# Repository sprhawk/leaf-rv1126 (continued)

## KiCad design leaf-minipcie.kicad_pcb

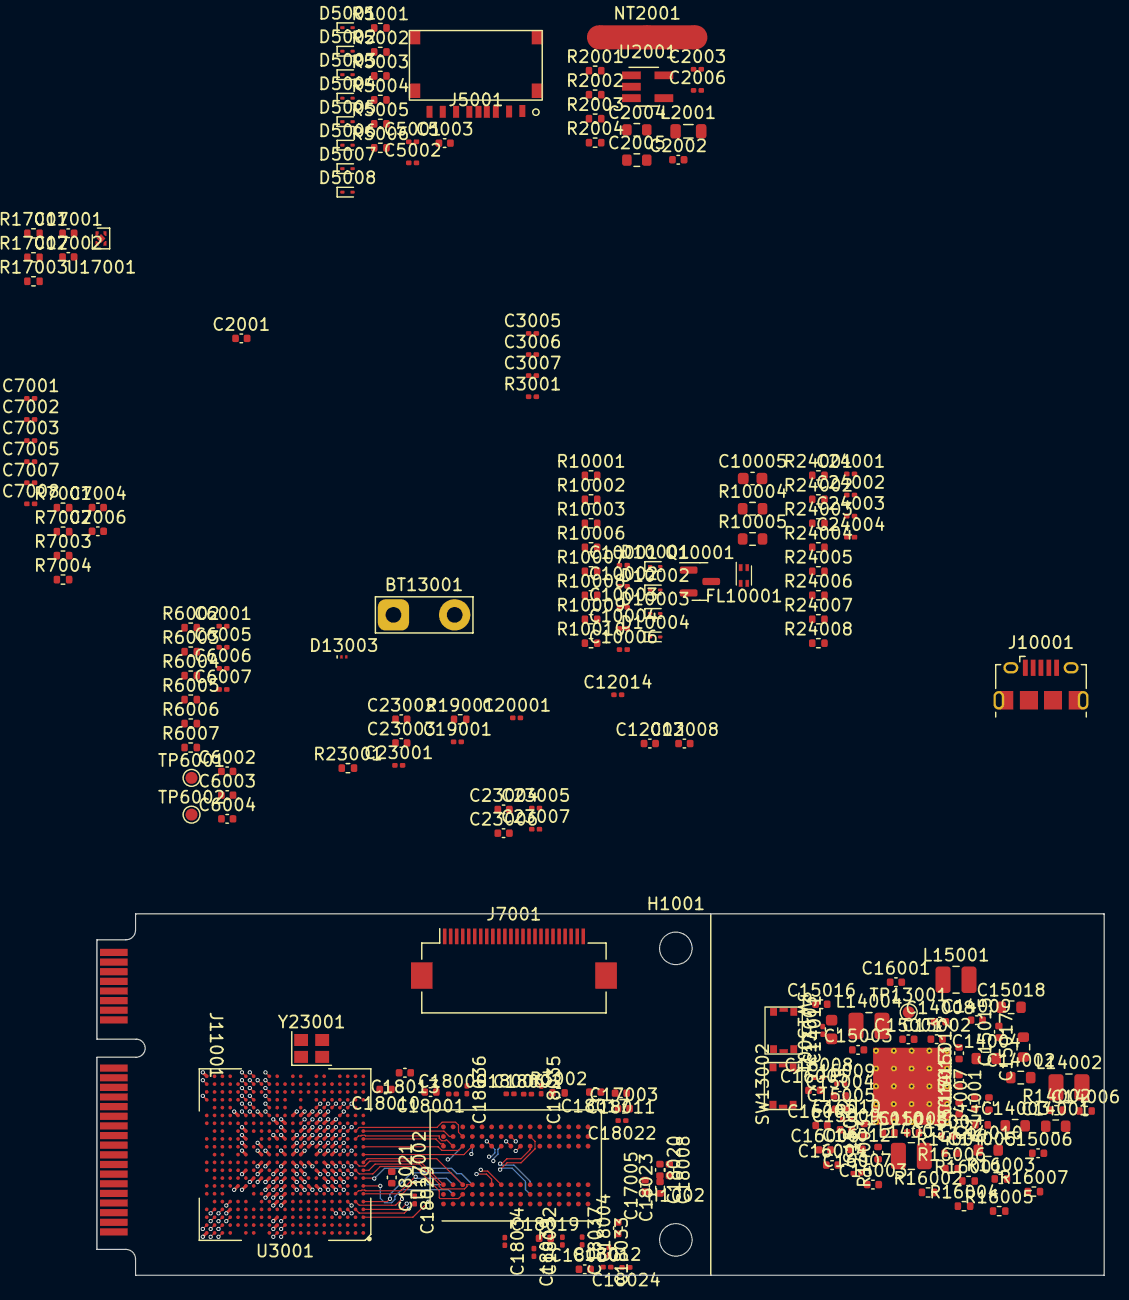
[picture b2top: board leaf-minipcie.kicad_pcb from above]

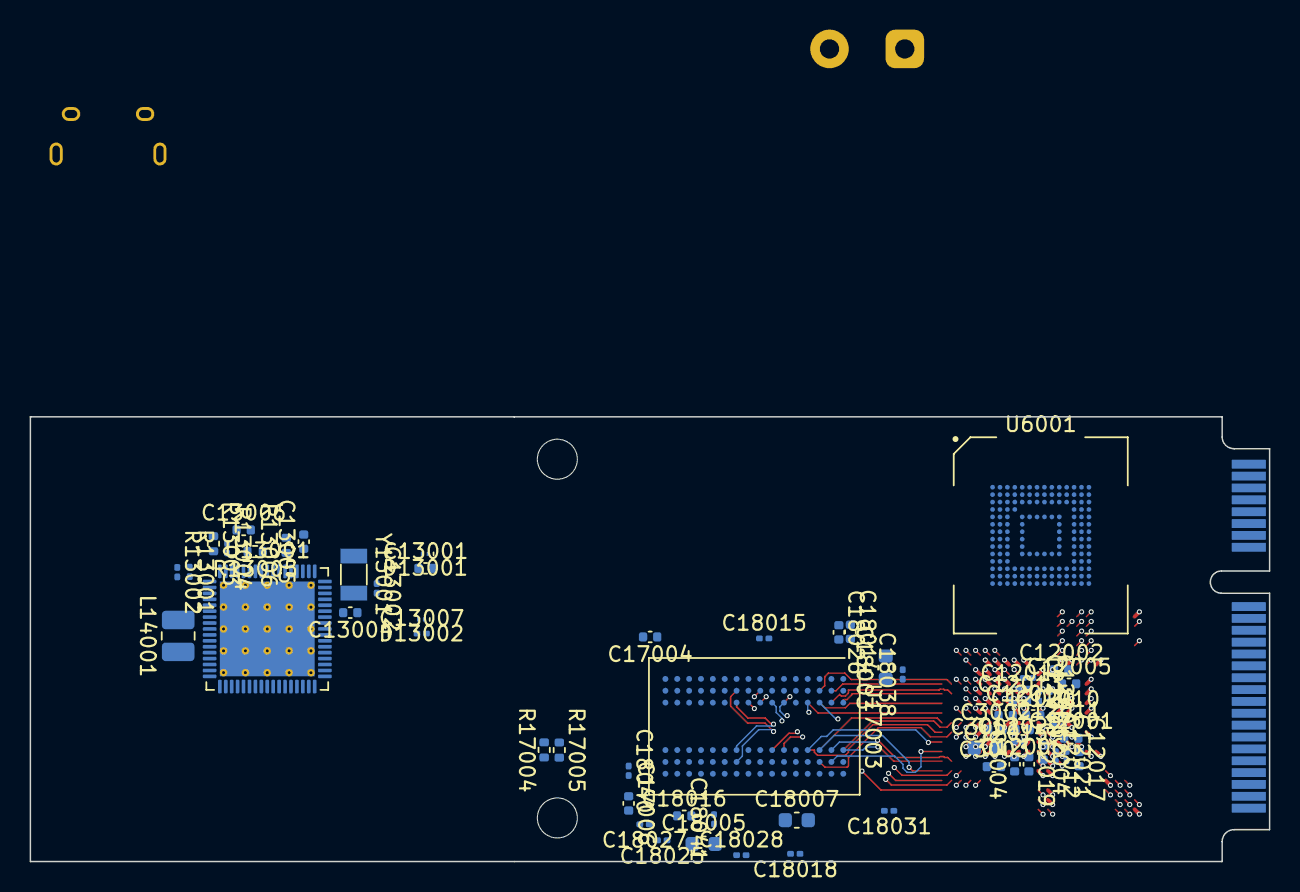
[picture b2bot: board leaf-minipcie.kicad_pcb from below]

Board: 6 copper layers, 83.6 x 30.0 mm, 275 parts (61 on the bottom side), 212 nets.

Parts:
BT13001: Battery_Cell; TestPoint_2Pads_Pitch5.08mm_Drill1.3mm
C2001, C5003, C12001, C12002, C12003, C12008, C12013, C12017, C14007, C14008, C14009, C15005, C16001: 10uF X5R 10V; C_0402_1005Metric
C2002, C18004, C18008, C18010, C18011, C18013, C18014, C18016, C18019, C18020, C18023, C18026: 100nF X5R 10V; C_0402_1005Metric
C2003, C13002, C13003: 22pF 50V C0G; C_0201_0603Metric
C2004, C2005, C14001, C14002, C14003, C14004, C14010, C15017, C15018: 22uF X5R 10V; R_0603_1608Metric
C2006, C3005, C3006, C3007, C5001, C5002, C6001, C6005, C6006, C6007, C7001, C7002, C7003, C7005, C7007, C7008, C10001, C10002, C10003, C10004, C10006, C12007, C12009, C12010, C12011, C12012, C12014, C12016, C12018, C12021, C12022, C13007, C16009, C16010, C18002, C18006, C18009, C18012, C18015, C18018, C18022, C18024, C18025, C18027, C18028, C18029, C18031, C18032, C18033, C18034, C18035, C18036, C18037, C18038, C18039, C18040, C18041, C19001, C20001, C23001, C23005, C23007: 100nF X5R 6.3V; C_0201_0603Metric
C3001: 10uF X5R 6.3V; C_0603_1608Metric
C3002, C3003, C3004, C12004, C12005, C12006, C12015, C12019, C12020, C13004, C13005, C15001, C15002, C15003, C15004, C16002, C16004, C16005, C23004, C23006: 1uF X5R 6.3V; C_0402_1005Metric
C6002, C6003, C6004, C15009, C18001, C18017: 4.7uF X5R 10V; C_0402_1005Metric
C7004, C7006: 10uF X5R 6.3V; C_0402_1005Metric
C10005, C14011: 22uF X5R 10V; C_0603_1608Metric
C13001: 100nF X5R 6.3V; C_0402_1005Metric
C13006: 10nF 25V X5R; C_0402_1005Metric
C14005, C14006, C14012: 10uF X5R 6.3V; R_0402_1005Metric
C15006, C15007, C15008, C15010, C15011, C15012, C15013, C15014, C15015, C15016: 1uF X5R 10V; C_0402_1005Metric
C16003, C16006: 2.2uF X5R 10V; C_0402_1005Metric
C16007, C16008: 27pF C0G 50V; C_0201_0603Metric
C17001, C17002: 1uF ±10% 6.3V; C_0402_1005Metric
C17003, C17005: 10nF X5R 50V; C_0402_1005Metric
C17004, C17006, C18021, C18030: 1nF X5R 50V; C_0402_1005Metric
C18003, C18005, C18007: 22uF X5R 6.3V; C_0603_1608Metric
C23002, C23003: 10pF 50V C0G +-1%; C_0402_1005Metric
C24001, C24003: 1nF X5R 25V; C_0201_0603Metric
C24002, C24004: 100pF C0G 50V; C_0201_0603Metric
D5001, D5002, D5003, D5004, D5005, D5006, D5007, D5008, D10001, D10002, D10003, D10004: ESD9B5.0ST5G; D_SOD-923
D13001: ESD 3.3V; Nexperia_DSN0603-2_0.6x0.3mm_P0.4mm
D13002, D13003: ESD 5.0V; Nexperia_DSN0603-2_0.6x0.3mm_P0.4mm
FL10001: Filter_EMI_CommonMode; L_CommonModeChoke_Coilcraft_0603USB
H1001, H1002: MountingHole; MountingHole_2.7mm_M2.5
J5001: Micro_SD_Card_Det1; microSD
J7001: MIPI-CSI; Hirose_FH12-24S-0.5SH_1x24-1MP_P0.50mm_Horizontal
J10001: USB_OTG; USB_Micro-B_Amphenol_10118194_Horizontal
J11001: mini PCIe Card edge; PCIe_MiniCard
L2001: 2.2uH 0.102 ohm 2.30A; L_0805_2012Metric
L14001, L14002, L14003, L14004, L15001: 470nH 4.53A 0.035ohm; L_1008_2520Metric
NT2001: NetTie_3_Tee; NetTie-3_SMD_Pad2.0mm
Q10001: Q_PNP_BEC; SOT-23
R2001: 56K 1%; R_0402_1005Metric
R2002, R10008, R14001, R14002: 100R 5%; R_0402_1005Metric
R2003: 43.2K 1%; R_0402_1005Metric
R2004: 115K 1%; R_0402_1005Metric
R3001: 240R 1%; R_0201_0603Metric
R3002, R6004, R6005, R7003, R7004, R16007, R19001: 0R 5%; R_0402_1005Metric
R5001, R5002, R5003, R5004, R5005, R5006, R13003, R16001, R16002, R16003, R16004, R16005, R16006, R23001: 22R 5%; R_0402_1005Metric
R6002, R6003, R6006, R6007: 4.7K 5%; R_0402_1005Metric
R7001, R7002, R10001: 2.2K 5%; R_0402_1005Metric
R10002: 1K 5%; R_0402_1005Metric
R10003: 220R 5%; R_0402_1005Metric
R10004, R10005: 2.2R 5%; R_0603_1608Metric
R10006, R10007: 200R 1%; R_0402_1005Metric
R10009: 18K 1%; R_0402_1005Metric
R10010, R17004, R17005: 10K 1%; R_0402_1005Metric
R13001, R13002: 2.2kΩ ±5%; R_0201_0603Metric
R13004: 4.7K 5%; R_0201_0603Metric
R13005: 450K 1%; R_0402_1005Metric
R13006: 47K 1%; R_0402_1005Metric
R14003: 120K 1%; R_0402_1005Metric
R14004: 110K 1%; R_0402_1005Metric
R17001, R17002, R17003: 240R 1%; R_0402_1005Metric
R24001, R24002, R24005, R24006: 1K 1%; R_0402_1005Metric
R24003, R24004, R24007, R24008: 49.9R 1%; R_0402_1005Metric
SW13001, SW13002: SKSGPAE010; SW_SPST_ALPS_SKSG_3.9x2.7mm
TP6001, TP6002, TP13001: TestPoint; TestPoint_Pad_D1.0mm
U2001: BL8039; SOT-23-5_HandSoldering
U3001: rv1126/rv1109; Rockchip_RV1126_FCCSP409LD_14.0x14.0mm
U6001: MTFC4GACAJCN; Micron_eMMC_FBGA-153_11.5x13.0mm
U13001: RK809-2; QFN-68-1EP_8x8mm_P0.4mm_EP6.4x6.4mm_ThermalVias
U17001: NCP114AMX250TCG; OnSemi_XDFN4-1EP_1.0x1.0mm_EP0.52x0.52mm
U17002, U17003: Samsung K4A4G165WE-BCRC; Micron_FBGA-96_9x14mm_Layout9x16_P0.8mm
Y13001: 32.768kHz ±20ppm 12.5pF; Crystal_SMD_3215-2Pin_3.2x1.5mm
Y23001: 24MHz ±10ppm 10pF; Crystal_SMD_2520-4Pin_2.5x2.0mm

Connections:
/DDR/DDR4_A0: U3001.C9 (LPDDR4_CKE1_A/DDR4_A0/LPDDR3_A3/DDR3_A3), U17002.P3 (A0), U17003.P3 (A0)
/DDR/DDR4_A1: U3001.B7 (LPDDR4_CKE0_B/DDR4_A1/DDR3_BA1), U17002.P7 (A1), U17003.P7 (A1)
/DDR/DDR4_A2: U3001.B11 (LPDDR4_A4_A/DDR4_A2/LPDDR3_A9/DDR3_A9), U17002.R3 (A2), U17003.R3 (A2)
/DDR/DDR4_A3: U3001.B6 (LPDDR4_A5_B/DDR4_A3/DDR3_A15), U17002.N7 (A3), U17003.N7 (A3)
/DDR/DDR4_A4: U3001.A9 (LPDDR4_CLKP_A/DDR4_A4/LPDDR3_A6/DDR3_A6), U17002.N3 (A4), U17003.N3 (A4)
/DDR/DDR4_A5: U3001.A7 (LPDDR4_ODT0_B/DDR4_A5/DDR3_A12), U17002.P8 (A5), U17003.P8 (A5)
/DDR/DDR4_A6: U3001.C8 (LPDDR4_A0_A/DDR4_A6/DDR3_BA2), U17002.P2 (A6), U17003.P2 (A6)
/DDR/DDR4_A7: U3001.B8 (LPDDR4_ODT0_A/DDR4_A7/LPDDR3_A4/DDR3_A4), U17002.R8 (A7), U17003.R8 (A7)
/DDR/DDR4_A8: U3001.A8 (LPDDR4_CKE0_A/DDR4_A8/LPDDR3_A1/DDR3_A1), U17002.R2 (A8), U17003.R2 (A8)
/DDR/DDR4_A9: U3001.B9 (LPDDR4_A5_A/DDR4_A9/LPDDR3_A5/DDR3_A5), U17002.R7 (A9), U17003.R7 (A9)
/DDR/DDR4_A10: U3001.A10 (LPDDR4_CLKN_A/DDR4_A10/LPDDR3_A8/DDR3_A8), U17002.M3 (A10/AP), U17003.M3 (A10/AP)
/DDR/DDR4_A11: U3001.C11 (LPDDR4_A2_A/DDR4_A11/LPDDR3_A7/DDR3_A7), U17002.T2 (A11), U17003.T2 (A11)
/DDR/DDR4_A12: U3001.D7 (LPDDR4_A1_A/DDR4_A12/DDR3_RASn), U17002.M7 (A12/~BC), U17003.M7 (A12/~BC)
/DDR/DDR4_A13: U3001.A12 (LPDDR4_A3_A/DDR4_A13/DDR3_A13), U17002.T8 (A13), U17003.T8 (A13)
/DDR/DDR4_A14_~WE: U3001.A11 (LPDDR4_CS1n_B/DDR4_A14_Wen/DDR3_A14), U17002.L2 (A14/~WE), U17003.L2 (A14/~WE)
/DDR/DDR4_A15_~CAS: U3001.B5 (LPDDR4_A0_B/DDR4_A15_CASn/DDR3_A10), U17002.M8 (A15/~CAS), U17003.M8 (A15/~CAS)
/DDR/DDR4_A16_~RAS: U3001.B10 (LPDDR4_CS0n_B/DDR4_A16_RASn/DDR3_A11), U17002.L8 (A16/~RAS), U17003.L8 (A16/~RAS)
/DDR/DDR4_BA0: U3001.E7 (LPDDR4_CS0n_A/DDR4_BA0/LPDDR3_CS1n/DDR3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), U17002.N2 (BA0), U17003.N2 (BA0)
/DDR/DDR4_BA1: U3001.A6 (LPDDR4_CKE1_B/DDR4_BA1/DDR3_WEn), U17002.N8 (BA1), U17003.N8 (BA1)
/DDR/DDR4_BG0: U3001.D6 (LPDDR4_CS1n_A/DDR4_BG0/LPDDR3_ODT1/DDR3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), U17002.M2 (BG0), U17003.M2 (BG0)
/DDR/DDR4_CKE: U3001.C6 (LPDDR4_A1_B/DDR4_CKE/DDR3_CASn), U17002.K2 (CKE), U17003.K2 (CKE)
/DDR/DDR4_CLKN: R24004.1, R24008.1, U3001.D5 (LPDDR4_CLKN_B/DDR4_CLKN/LPDDR3_CLKN/DDR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), U17002.K8 (CK#), U17003.K8 (CK#)
/DDR/DDR4_CLKP: R24003.1, R24007.1, U3001.D4 (LPDDR4_CLKP_B/DDR4_CLKP/LPDDR3_CLKP/DDR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), U17002.K7 (CK), U17003.K7 (CK)
/DDR/DDR4_D0: U3001.K4 (DDR_DQ0/LPDDR4_D8_A/LPDDR3_D2), U17002.J3 (DQ6)
/DDR/DDR4_D1: U3001.J4 (DDR_DQ1/LPDDR4_D9_A/LPDDR3_D6), U17002.G2 (DQ0)
/DDR/DDR4_D2: U3001.P4 (DDR_DQ2/LPDDR4_D10_A/LPDDR3_D4), U17002.H7 (DQ3)
/DDR/DDR4_D3: U3001.N4 (DDR_DQ3/LPDDR4_D11_A/LPDDR3_D0), U17002.H8 (DQ5)
/DDR/DDR4_D4: U3001.J3 (DDR_DQ4/LPDDR4_D12_A/LPDDR3_D3), U17002.H2 (DQ4)
/DDR/DDR4_D5: U3001.K3 (DDR_DQ5/LPDDR4_D13_A/LPDDR3_D7), U17002.H3 (DQ2)
/DDR/DDR4_D6: U3001.M4 (DDR_DQ6/LPDDR4_D14_A/LPDDR3_D5), U17002.J7 (DQ7)
/DDR/DDR4_D7: U3001.P3 (DDR_DQ7/LPDDR4_D15_A/LPDDR3_D1), U17002.F7 (DQ1)
/DDR/DDR4_D8: U3001.D2 (DDR_DQ8/LPDDR4_D10_B/LPDDR3_D0), U17003.C3 (DQ10)
/DDR/DDR4_D9: U3001.D1 (DDR_DQ9/LPDDR4_D1_B/LPDDR3_D11), U17003.D3 (DQ14)
/DDR/DDR4_D10: U3001.H2 (DDR_DQ10/LPDDR4_D2_B/LPDDR3_D8), U17003.C8 (DQ13)
/DDR/DDR4_D11: U3001.H1 (DDR_DQ11/LPDDR4_D3_B/LPDDR3_D9), U17003.D7 (DQ15)
/DDR/DDR4_D12: U3001.G1 (DDR_DQ12/LPDDR4_D4_B/LPDDR3_D12), U17003.B8 (DQ9)
/DDR/DDR4_D13: U3001.E1 (DDR_DQ13/LPDDR4_D5_B/LPDDR3_D13), U17003.C7 (DQ11)
/DDR/DDR4_D14: U3001.C1 (DDR_DQ14/LPDDR4_D6_B/LPDDR3_D14), U17003.C2 (DQ12)
/DDR/DDR4_D15: U3001.C2 (DDR_DQ15/LPDDR4_D7_B/LPDDR3_D15), U17003.A3 (DQ8)
/DDR/DDR4_D16: U3001.K1 (DDR_DQ16/LPDDR4_D0_A/LPDDR3_D19), U17002.C3 (DQ10)
/DDR/DDR4_D17: U3001.K2 (DDR_DQ17/LPDDR4_D1_A/LPDDR3_D18), U17002.A3 (DQ8)
/DDR/DDR4_D18: U3001.J1 (DDR_DQ18/LPDDR4_D2_A/LPDDR3_D23), U17002.D3 (DQ14)
/DDR/DDR4_D19: U3001.J2 (DDR_DQ19/LPDDR4_D3_A/LPDDR3_D22), U17002.C2 (DQ12)
/DDR/DDR4_D20: U3001.P2 (DDR_DQ20/LPDDR4_D4_A/LPDDR3_D21), U17002.C8 (DQ13)
/DDR/DDR4_D21: U3001.L1 (DDR_DQ21/LPDDR4_D5_A/LPDDR3_D16), U17002.D7 (DQ15)
/DDR/DDR4_D22: U3001.M1 (DDR_DQ22/LPDDR4_D6_A/LPDDR3_D17), U17002.C7 (DQ11)
/DDR/DDR4_D23: U3001.P1 (DDR_DQ23/LPDDR4_D7_A/LPDDR3_D20), U17002.B8 (DQ9)
/DDR/DDR4_D24: U3001.A2 (DDR_DQ24/LPDDR4_D8_B/LPDDR3_D30), U17003.H2 (DQ4)
/DDR/DDR4_D25: U3001.A3 (DDR_DQ25/LPDDR4_D9_B/LPDDR3_D31), U17003.G2 (DQ0)
/DDR/DDR4_D26: U3001.G4 (DDR_DQ26/LPDDR4_D10_B/LPDDR3_D28), U17003.F7 (DQ1)
/DDR/DDR4_D27: U3001.F4 (DDR_DQ27/LPDDR4_D11_B/LPDDR3_D29), U17003.J7 (DQ7)
/DDR/DDR4_D28: U3001.H3 (DDR_DQ28/LPDDR4_D12_B/LPDDR3_D24), U17003.H8 (DQ5)
/DDR/DDR4_D29: U3001.G3 (DDR_DQ29/LPDDR4_D13_B/LPDDR3_D25), U17003.H7 (DQ3)
/DDR/DDR4_D30: U3001.B1 (DDR_DQ30/LPDDR4_D14_B/LPDDR3_D26), U17003.H3 (DQ2)
/DDR/DDR4_D31: U3001.B2 (DDR_DQ31/LPDDR4_D15_B/LPDDR3_D27), U17003.J3 (DQ6)
/DDR/DDR4_DM0: U3001.N3 (DDR_DM0/LPDDR4_DM1_A/LPDDR3_DM0), U17002.E7 (NF/~LDM/~LDBI)
/DDR/DDR4_DM1: U3001.E2 (DDR_DM1/LPDDR4_DM0_B/LPDDR3_DM1), U17003.E7 (NF/~LDM/~LDBI)
/DDR/DDR4_DM2: U3001.M2 (DDR_DM2/LPDDR4_DM0_A/LPDDR3_DM2), U17002.E2 (NF/~UDM/~UDBI)
/DDR/DDR4_DM3: U3001.B3 (DDR_DM3/LPDDR4_DM1_B/LPDDR3_DM3), U17003.E2 (NF/~UDM/~UDBI)
/DDR/DDR4_DQS0N: U3001.L3 (DDR_DQS0N/LPDDR4_DQS1N_A/LPDDR3_DQS0N), U17002.F3 (LDQS#)
/DDR/DDR4_DQS0P: U3001.L4 (DDR_DQS0P/LPDDR4_DQS1P_A/LPDDR3_DQS0P), U17002.G3 (LDQS)
/DDR/DDR4_DQS1N: U3001.F1 (DDR_DQS1N/LPDDR4_DQS0N_B/LPDDR3_DQS1N), U17003.A7 (UDQS#)
/DDR/DDR4_DQS1P: U3001.F2 (DDR_DQS1P/LPDDR4_DQS0P_B/LPDDR3_DQS01P), U17003.B7 (UDQS)
/DDR/DDR4_DQS2N: U3001.N1 (DDR_DQS2N/LPDDR4_DQS0N_A/LPDDR3_DQS2N), U17002.A7 (UDQS#)
/DDR/DDR4_DQS2P: U3001.N2 (DDR_DQS2P/LPDDR4_DQS0P_A/LPDDR3_DQS2P), U17002.B7 (UDQS)
/DDR/DDR4_DQS3N: U3001.E3 (DDR_DQS3N/LPDDR4_DQS1N_B/LPDDR3_DQS3N), U17003.F3 (LDQS#)
/DDR/DDR4_DQS3P: U3001.D3 (DDR_DQS3P/LPDDR4_DQS1P_B/LPDDR3_DQS3P), U17003.G3 (LDQS)
/DDR/DDR4_ODT0: U3001.A5 (LPDDR4_A4_B/DDR4_ODT0/LPDDR3_CS0n/DDR3_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), U17002.K3 (ODT), U17003.K3 (ODT)
/DDR/DDR4_~ACT: U3001.A4 (LPDDR4_A3_B/DDR4_ACTn/LPDDR3_CKE/DDR3_C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), U17002.L3 (~ACT), U17003.L3 (~ACT)
/DDR/DDR4_~CS0: U3001.B4 (LPDDR4_A2_B/DDR4_CS0n/LPDDR3_ODT0/DDR3_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), U17002.L7 (~CS), U17003.L7 (~CS)
/DDR/DDR Power/VCC25_DDR: C17002.1, C18001.1, C18004.2, C18008.2, C18011.2, C18014.2, C18017.1, C18020.2, C18023.2, C18026.2, U17001.1 (OUT), U17002.B1 (V_{PP}), U17002.R9 (V_{PP}), U17003.B1 (V_{PP}), U17003.R9 (V_{PP})
/DDR/DDR_VREFCA: C17003.1, C17004.1, C17005.1, C17006.1, R3002.2, R17004.2, R17005.1, U17002.M1 (V_{REFCA}), U17003.M1 (V_{REFCA})
/DDR/DDR_~RESET: C24001.1, C24003.1, U3001.C4 (DDR_RESETn), U17002.P1 (~RESET), U17003.P1 (~RESET)
/DDR/VREF_DDR: R3002.1, U3001.M6 (DDR_VREF)
/PMIC_CLK32K: R13003.1, U3001.AA3 (CLKI_CLKO_32K/GPIO0_A2_z)
/PMIC_I2C_SCL: R13002.2, U3001.AA7 (I2C0_SCL/GPIO0_B4_u), U13001.2 (SDA)
/PMIC_I2C_SDA: R13001.2, U3001.Y7 (I2C0_SDA/GPIO0_B5_u), U13001.1 (SCL)
/PMIC_INT: U3001.W10 (PMIC_INT/PWM7_IR_M0/GPIO0_B1_d), U13001.7 (INT)
/PMIC_RESET: C13001.1, C23001.1, D13001.2 (A2), R13004.2, R19001.1, SW13001.1, U3001.W7 (nPOR_u), U13001.67 (RESETB)
/PMIC_SLEEP: U3001.Y10 (PMIC_SLEEP/TSADC_SHUT_M1/PWM6_M0/GPIO0_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), U13001.49 (SLEEP)
/PMUIO0/SD_DET: D5001.1 (A1), J5001.9 (DET), U3001.U7 (SDMMC0_DET/GPIO0_A3_u)
/PMUIO1/FLASH_VOL_SEL: R6002.1, R6003.2, U3001.Y8 (FLASH_VOL_SEL/GPIO0_B3_d)
/Power/PMIC/RK809 Codec/I2S_LRCLK_TX: R16003.2, U13001.14 (LRCLK)
/Power/PMIC/RK809 Codec/I2S_MCLK: R16001.2, U13001.16 (MCLK)
/Power/PMIC/RK809 Codec/I2S_SCLK_TX: R16002.2, U13001.15 (BCLK)
/Power/PMIC/RK809 Codec/I2S_SDI0: R16005.2, U13001.18 (SDO/PDMDATA)
/Power/PMIC/RK809 Codec/I2S_SDO0: R16004.2, U13001.17 (SDI)
/Power/PMIC/RK809 Management/PWR_ON: C13007.1, D13002.2 (A2), SW13002.1, U13001.52 (PWRON)
/SoC OSC PLL/XIN24M: C23003.2, U3001.AA9 (XIN24M), Y23001.1
/SoC OSC PLL/XOUT24M: R23001.1, U3001.Y9 (XOUT24M)
/USB/OTG_DET_1V8: C10006.1, R10009.1, R10010.2, U3001.V5 (OTG_VBUS_1V8)
/USB/OTG_DM: FL10001.3, R10003.2, R10005.1, U3001.W4 (OTG_DM)
/USB/OTG_DP: FL10001.1, R10004.1, U3001.W3 (OTG_DP)
/USB/OTG_ID: R10008.1, U3001.Y3 (OTG_ID)
/USB/OTG_PORT_DM: D10004.1 (A1), FL10001.4, J10001.2 (D-), R10005.2
/USB/OTG_PORT_DP: D10002.1 (A1), FL10001.2, J10001.3 (D+), R10004.2
/USB_CTRL: R10001.2, U3001.AA4 (USB_CTRL/PMU_DEBUG/UART1_CTSN_M0/PWM3_I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)
/VCCIO1/EMMC_CLK: R6004.1, U6001.M6 (CLK)
/VCCIO1/EMMC_CMD: R6006.1, U3001.T4 (FLASH_WRn/EMMC_CMD/GPIO0_D5_u), U6001.M5 (CMD)
/VCCIO1/EMMC_D0: R6007.1, TP6001.1, U3001.W2 (FLASH_D0/EMMC_D0/GPIO0_C4_u), U6001.A3 (DATA0)
/VCCIO1/EMMC_D1: U3001.W1 (FLASH_D1/EMMC_D1/GPIO0_C5_u), U6001.A4 (DATA1)
/VCCIO1/EMMC_D2: U3001.V4 (FLASH_D2/EMMC_D2/GPIO0_C6_u), U6001.A5 (DATA2)
/VCCIO1/EMMC_D3: U3001.V3 (FLASH_D3/EMMC_D3/GPIO0_C7_u), U6001.B2 (DATA3)
/VCCIO1/EMMC_D4: U3001.V2 (FLASH_D4/EMMC_D4/GPIO0_D0_u), U6001.B3 (DATA4)
/VCCIO1/EMMC_D5: U3001.V1 (FLASH_D5/EMMC_D5/FSPI_CS1n/GPIO0_D1_u), U6001.B4 (DATA5)
/VCCIO1/EMMC_D6: U3001.U4 (FLASH_D6/EMMC_D6/GPIO0_D2_u), U6001.B5 (DATA6)
/VCCIO1/EMMC_D7: U3001.U3 (FLASH_D7/EMMC_D7/GPIO0_D3_u), U6001.B6 (DATA7)
/VCCIO1/EMMC_~RST: R6005.1, U6001.K5 (~RST)
/VCCIO2/A7_JTAG_TCK: R5005.1, U3001.V13 (SDMMC0_D2/UART3_RX_M1/A7_JTAG_TCK_M0/RI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)
/VCCIO2/A7_JTAG_TMS: R5006.1, U3001.U13 (SDMMC0_D3/UART3_TX_M1/A7_JTAG_TMS_M0/RI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)
/VCCIO2/RV_JTAG_TDI: R5002.1, U3001.Y13 (SDMMC0_CMD/UART3_CTSN_M1/RISC-V_JTAG_TD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)
/VCCIO2/RV_JTAG_TDO: R5001.1, U3001.AA13 (SDMMC0_CLK/UART3_RTSN_M1/RISC-V_JTAG_TD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)
/VCCIO2/RV_JTAG_TRSTn: R5004.1, U3001.W13 (SDMMC0_D1/TEST_CLK0_OUT/UART2_TX_M0/RIS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)
/VCCIO2/SD_CLK: D5004.1 (A1), J5001.5 (CLK), R5001.2
/VCCIO2/SD_CMD: D5006.1 (A1), J5001.3 (CMD), R5002.2
/VCCIO2/SD_D0: D5003.1 (A1), J5001.7 (DAT0), R5003.2
/VCCIO2/SD_D1: D5002.1 (A1), J5001.8 (DAT1), R5004.2
/VCCIO2/SD_D2: D5008.1 (A1), J5001.1 (DAT2), R5005.2
/VCCIO2/SD_D3: D5007.1 (A1), J5001.2 (DAT3/CD), R5006.2
/VCCIO4/MIPI_CSI_AVDD_0V8: C7003.1, R7004.2, U3001.T15 (MIPI_CSI_RX0_AVDD_0V8)
/VCCIO4/MIPI_CSI_AVDD_1V8: C7001.1, R7003.2, U3001.T16 (MIPI_CSI_RX0_AVDD_1V8)
/VCCIO4/MIPI_CSI_I2C_SCL: J7001.6, R7002.1, U3001.Y21 (I2C1_SCL/UART4_CTSN_M2/GPIO1_D3_u)
/VCCIO4/MIPI_CSI_I2C_SDA: J7001.5, R7001.1, U3001.W19 (I2C1_SDA/UART4_RTSN_M2/GPIO1_D2_u)
/VCCIO4/MIPI_CSI_MCLK0: J7001.21, U3001.V21 (MIPI_CSI_CLK0/UART5_CTSN_M2/GPIO2_A3_d)
/VCCIO4/MIPI_CSI_PWR0: J7001.3, U3001.W20 (UART4_RX_M2/GPIO1_D4_d)
/VCCIO4/MIPI_CSI_RST0: J7001.4, U3001.V19 (SPI0_MOSI_M1/I2S1_SCLK_M1/I2C3_SCL_M2/G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)
/VCCIO4/MIPI_RX0_CLKN: J7001.18, U3001.V15 (MIPI_CSI_RX0_CLKN/LVDS0_CLKN)
/VCCIO4/MIPI_RX0_CLKP: J7001.19, U3001.U15 (MIPI_CSI_RX0_CLKP/LVDS0_CLKP)
/VCCIO4/MIPI_RX0_D0N: J7001.9, U3001.U16 (MIPI_CSI_RX0_D0N/LVDS0_RX0N)
/VCCIO4/MIPI_RX0_D0P: J7001.10, U3001.V16 (MIPI_CSI_RX0_D0P/LVDS0_RX0P)
/VCCIO4/MIPI_RX0_D1N: J7001.11, U3001.W16 (MIPI_CSI_RX0_D1N/LVDS0_RX1N)
/VCCIO4/MIPI_RX0_D1P: J7001.12, U3001.Y16 (MIPI_CSI_RX0_D1P/LVDS0_RX1P)
/VCCIO4/MIPI_RX0_D2N: J7001.13, U3001.Y15 (MIPI_CSI_RX0_D2N/LVDS0_RX2N)
/VCCIO4/MIPI_RX0_D2P: J7001.14, U3001.W15 (MIPI_CSI_RX0_D2P/LVDS0_RX2P)
/VCCIO4/MIPI_RX0_D3N: J7001.15, U3001.AA16 (MIPI_CSI_RX0_D3N/LVDS0_RX3N)
/VCCIO4/MIPI_RX0_D3P: J7001.16, U3001.AA15 (MIPI_CSI_RX0_D3P/LVDS0_RX3P)
/VCCIO4/VCC1V8_DOVDD: C7008.1, J7001.22, R7001.2, R7002.2
/VCCIO4/VCCAVDD_RGB: C7004.1, C7005.1, J7001.24
/VCCIO4/VCCDVDD_RGB: C7006.1, C7007.1, J7001.23
/mini PCIe/mPCIe_1V5: J11001.6, J11001.28, J11001.48
/mini PCIe/mPCIe_3V3_aux: J11001.2, J11001.24, J11001.39, J11001.41, J11001.52
/mini PCIe/mPCIe_GND: J11001.4, J11001.9, J11001.15, J11001.18, J11001.21, J11001.26, J11001.27, J11001.29, J11001.34, J11001.35, J11001.37, J11001.40, J11001.43, J11001.50
/mini PCIe/mPCIe_Reserved: J11001.17, J11001.19, J11001.45, J11001.47, J11001.49, J11001.51
GND: C3001.1, C3002.1, C3002.2, C3003.1, C3004.1, C3005.1, C3006.1, C3007.1, C5001.2, C5002.2, C5003.2, C6001.2, C6002.2, C6003.2, C6004.2, C6005.2, C6006.2, C6007.2, C7002.2, C7004.2, C7005.2, C7006.2, C7007.2, C7008.2, C10001.2, C10002.2, C10003.2, C10004.1, C10005.1, C10006.2, C12001.2, C12002.2, C12003.2, C12004.2, C12005.2, C12006.2, C12007.2, C12008.2, C12009.2, C12010.2, C12011.2, C12012.1, C12012.2, C12013.2, C12014.2, C12015.2, C12016.2, C12017.1, C12017.2, C12018.1, C12018.2, C12019.2, C12020.2, C12021.1, C12021.2, C13001.2, C13002.1, C13003.1, C13004.1, C13005.2, C13006.2, C13007.2, C14001.2, C14002.2, C14003.2, C14004.2, C14005.2, C14006.2, C14007.1, C14008.1, C14009.1, C14010.2, C14011.1, C14012.2, C15001.2, C15002.2, C15003.2, C15004.2, C15005.2, C15006.2, C15007.2, C15008.2, C15009.2, C15010.2, C15011.2, C15012.2, C15013.2, C15014.2, C15015.2, C15016.2, C15017.2, C15018.2, C16001.2, C16002.2, C16003.2, C16004.2, C16005.2, C16007.2, C16008.2, C17001.2, C17002.2, C17003.2, C17004.2, C17005.2, C17006.2, C18001.2, C18002.1, C18003.1, C18004.1, C18005.1, C18006.1, C18007.1, C18008.1, C18009.1, C18010.1, C18011.1, C18012.1, C18013.1, C18014.1, C18015.1, C18016.1, C18017.2, C18018.1, C18019.1, C18020.1, C18021.1, C18022.1, C18023.1, C18024.1, C18025.1, C18026.1, C18027.1, C18028.1, C18029.1, C18030.1, C18031.1, C18032.1, C18033.1, C18034.1, C18035.1, C18036.1, C18037.1, C18038.1, C18039.1, C18040.1, C18041.1, C19001.2, C20001.2, C23001.2, C23002.1, C23003.1, C23004.2, C23005.2, C23006.2, C23007.2, C24001.2, C24002.2, C24003.2, C24004.2, D5001.2 (A2), D5002.2 (A2), D5003.2 (A2), D5004.2 (A2), D5005.2 (A2), D5006.2 (A2), D5007.2 (A2), D5008.2 (A2), D10001.2 (A2), D10002.2 (A2), D10003.2 (A2), D10004.2 (A2), D13001.1 (A1), D13002.1 (A1), D13003.1 (A1), J5001.6 (VSS), J5001.10 (SHIELD), J7001.MP (MountPin), J10001.5 (GND), J10001.6 (Shield), NT2001.2, R3001.2, R6003.1, R10006.2, R10007.2, R10010.1, R13006.2, R14003.2, R16007.1, R17002.2, R17003.2, R17005.2, R24001.2, R24002.2, R24005.2, R24006.2, SW13001.2, SW13001.3 (GND), SW13002.2, SW13002.3 (GND), TP6002.1, U3001.A1 (VSS_1), U3001.A21 (AVSS_1), U3001.AA1 (VSS_95), U3001.AA10 (VSS_96), U3001.AA21 (VSS_97), U3001.B12 (VSS_2), U3001.C3 (VSS_3), U3001.C5 (VSS_4), U3001.C7 (VSS_5), U3001.C10 (VSS_6), U3001.C12 (VSS_7), U3001.D9 (VSS_8), U3001.D12 (VSS_9), U3001.D18 (AVSS_2), U3001.E4 (VSS_10), U3001.E6 (VSS_11), U3001.E8 (VSS_12), U3001.E9 (VSS_13), U3001.E10 (VSS_14), U3001.E11 (VSS_15), U3001.E12 (VSS_16), U3001.F3 (VSS_17), U3001.F5 (VSS_18), U3001.F6 (DDR_AVSS), U3001.F7 (VSS_19), U3001.F8 (VSS_20), U3001.F9 (VSS_21), U3001.F10 (VSS_22), U3001.F11 (VSS_23), U3001.F12 (VSS_24), U3001.F13 (VSS_25), U3001.F14 (AVSS_3), U3001.F15 (AVSS_4), U3001.G2 (VSS_26), U3001.G5 (VSS_27), U3001.G6 (VSS_28), U3001.G11 (VSS_30), U3001.G12 (VSS_31), U3001.G13 (VSS_32), U3001.G16 (AVSS_5), U3001.G17 (AVSS_6), U3001.H4 (VSS_33), U3001.H5 (VSS_34), U3001.H6 (VSS_35), U3001.H7 (VSS_36), U3001.H12 (NPU_VDD_2), U3001.H13 (LOGIC_VDD_2), U3001.H15 (VSS_38), U3001.J5 (VSS_39), U3001.J6 (VSS_40), U3001.J12 (VSS_41), U3001.J14 (VSS_42), U3001.J16 (VSS_43), U3001.K5 (VSS_44), U3001.K6 (VSS_45), U3001.K8 (VSS_46), U3001.K9 (VSS_47), U3001.K12 (VSS_48), U3001.K13 (VSS_49), U3001.K14 (VSS_50), U3001.L2 (VSS_51), U3001.L5 (VSS_52), U3001.L6 (VSS_53), U3001.L10 (LOGIC_VDD_5), U3001.L11 (VSS_54), U3001.L12 (VSS_55), U3001.L13 (VSS_56), U3001.L14 (VSS_57), U3001.L16 (VSS_58), U3001.M3 (VSS_59), U3001.M5 (VSS_60), U3001.M7 (VSS_61), U3001.M8 (VSS_62), U3001.M10 (VSS_63), U3001.M12 (VSS_64), U3001.M13 (VSS_65), U3001.M14 (VSS_66), U3001.M16 (VSS_67), U3001.N5 (VSS_68), U3001.N6 (VSS_69), U3001.N7 (VSS_70), U3001.N9 (VEPU_VDD_4), U3001.N10 (VSS_71), U3001.N11 (VSS_72), U3001.N13 (VSS_73), U3001.N14 (VSS_74), U3001.N16 (VSS_75), U3001.P5 (VSS_76), U3001.P7 (VSS_77), U3001.P8 (VSS_78), U3001.P9 (VSS_79), U3001.P14 (VSS_80), U3001.P16 (VSS_81), U3001.R1 (VSS_82), U3001.R5 (VSS_83), U3001.R12 (VSS_84), U3001.R13 (VSS_85), U3001.R14 (VSS_86), U3001.T6 (VSS_87), U3001.T8 (TVSS), U3001.T9 (VSS_88), U3001.T10 (VSS_89), U3001.T14 (VSS_90), U3001.T17 (VSS_91), U3001.V17 (VSS_92), U3001.W9 (VSS_93), U3001.W14 (VSS_94), U6001.A6 (V_{SS}), U6001.C4 (V_{SSQ}), U6001.E7 (V_{SS}), U6001.G5 (V_{SS}), U6001.H10 (V_{SS}), U6001.J5 (V_{SS}), U6001.K8 (V_{SS}), U6001.N2 (V_{SSQ}), U6001.N5 (V_{SSQ}), U6001.P4 (V_{SSQ}), U6001.P6 (V_{SSQ}), U13001.47 (GNDREF), U13001.69 (ePAD), U17001.2 (GND), U17001.5 (GND), U17002.A2 (V_{SSQ}), U17002.A8 (V_{SSQ}), U17002.B2 (V_{SS}), U17002.C9 (V_{SSQ}), U17002.D2 (V_{SSQ}), U17002.D8 (V_{SSQ}), U17002.E1 (V_{SS}), U17002.E3 (V_{SSQ}), U17002.E8 (V_{SSQ}), U17002.E9 (V_{SS}), U17002.F1 (V_{SSQ}), U17002.G8 (V_{SS}), U17002.H1 (V_{SSQ}), U17002.H9 (V_{SSQ}), U17002.K1 (V_{SS}), U17002.K9 (V_{SS}), U17002.M9 (V_{SS}), U17002.N1 (V_{SS}), U17002.T1 (V_{SS}), U17003.A2 (V_{SSQ}), U17003.A8 (V_{SSQ}), U17003.B2 (V_{SS}), U17003.C9 (V_{SSQ}), U17003.D2 (V_{SSQ}), U17003.D8 (V_{SSQ}), U17003.E1 (V_{SS}), U17003.E3 (V_{SSQ}), U17003.E8 (V_{SSQ}), U17003.E9 (V_{SS}), U17003.F1 (V_{SSQ}), U17003.G8 (V_{SS}), U17003.H1 (V_{SSQ}), U17003.H9 (V_{SSQ}), U17003.K1 (V_{SS}), U17003.K9 (V_{SS}), U17003.M9 (V_{SS}), U17003.N1 (V_{SS}), U17003.T1 (V_{SS}), Y23001.2, Y23001.4
GNDA: C2001.2, C2002.1, C2004.2, C2005.2, C2006.1, C7001.2, C7003.2, NT2001.1, R2004.2, U2001.2 (GND)
GNDD: J7001.1, J7001.2, J7001.7, J7001.8, J7001.17, J7001.20, NT2001.3
unnamed: C16002.1, U13001.38 (VCC_CPVDD)
unnamed: C16003.1, U13001.35 (VCC_CPVSS)
unnamed: C16004.1, U13001.48 (VCC_1P8D)
unnamed: C16005.1, U13001.44 (VCC_1P8A)
unnamed: C23002.2, R23001.2, Y23001.3
unnamed: C24002.1, R24003.2, R24004.2
unnamed: C24004.1, R24007.2, R24008.2
unnamed: D10001.1 (A1), J10001.4 (ID), R10008.2
unnamed: Q10001.1 (B), R10001.1, R10002.2
unnamed: Q10001.2 (E), R10003.1
unnamed: C2002.2, R2001.2, U2001.1 (EN)
unnamed: C2003.2, R2003.1, R2004.1, U2001.5 (FB)
unnamed: L2001.1, U2001.3 (SW)
unnamed: R19001.2, U3001.Y5 (TSADC_SHUT_M0/TSADC_SHUTORG/GPIO0_A1_z)
unnamed: R6004.2, U3001.T1 (FLASH_CLE/EMMC_CLKO/GPIO0_D7_d)
unnamed: R6005.2, U3001.R3 (FLASH_WPn/EMMC_RSTn/FSPI_CLK/GPIO1_A3_d)
unnamed: R5003.1, U3001.Y14 (SDMMC0_D0/TEST_CLK1_OUT/UART2_RX_M0/GPI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)
unnamed: R3001.1, U3001.E5 (DDR_RZQ)
unnamed: R10007.1, U3001.U5 (HOST_EXTR)
unnamed: R10006.1, U3001.U6 (OTG_EXTR)
unnamed: C6002.1, U6001.C2 (V_{DDIM})
unnamed: R13003.2, U13001.68 (CLK32K)
unnamed: TP13001.1, U13001.60 (EXT_EN)
unnamed: C13006.1, R13005.2, R13006.1, U13001.61 (VDC)
unnamed: C13004.2, U13001.46 (VREF)
unnamed: C13002.2, U13001.50 (XIN), Y13001.1
unnamed: C13003.2, U13001.51 (XOUT), Y13001.2
unnamed: L15001.2, U13001.53 (SW5)
unnamed: R14003.1, R14004.2, U13001.27 (FB3)
unnamed: L14001.2, U13001.12 (SW1)
unnamed: L14002.2, U13001.9 (SW2)
unnamed: L14003.2, U13001.25 (SW3)
unnamed: L14004.2, U13001.65 (SW4)
unnamed: C16006.1, U13001.36 (CPN)
unnamed: C16006.2, U13001.37 (CPP)
unnamed: C16008.1, C16010.2, U13001.42 (MICIN)
unnamed: C16007.1, C16009.2, U13001.43 (MICIP)
unnamed: R16006.2, R16007.2, U13001.19 (PDMCLK)
unnamed: R17001.2, U17001.3 (EN)
unnamed: R24002.1, U17002.T3 (PAR)
unnamed: R24001.1, U17002.N9 (TEN)
unnamed: R17002.1, U17002.F9 (ZQ)
unnamed: R24006.1, U17003.T3 (PAR)
unnamed: R24005.1, U17003.N9 (TEN)
unnamed: R17003.1, U17003.F9 (ZQ)
VCC1V8_DOVDD: C15010.1, U13001.29 (LDO5)
VCC3V3: R13001.1, R13002.1, R13004.1
VCC3V3_SYS: C14011.2, C15004.1, C17001.1, C19001.1, C20001.1, L14004.1, R6002.2, R17001.1, U3001.R8 (PMUIO1_VDD), U3001.R9 (PMUIO0_VDD), U13001.57 (VCC8), U13001.64 (FB4), U17001.4 (IN)
VCC5V0_SYS: BT13001.1 (+), C2001.1, C13005.1, C14007.2, C14008.2, C14009.2, C15003.1, C15005.1, C16001.1, D13003.2 (A2), R13005.1, U2001.4 (VIN), U13001.4 (VCC7), U13001.10 (VCC2), U13001.11 (VCC1), U13001.24 (VCC3), U13001.33 (VCC_SKP_HP), U13001.45 (VCC_RTC), U13001.54 (VCC9), U13001.66 (VCC4)
VCC5V0_USB: C10004.2, C10005.2, D10003.1 (A1), J10001.1 (VBUS), R10009.2
VCCAVDD_RGB: C15012.1, U13001.3 (LDO7)
VCCDVDD_RGB: C15011.1, U13001.31 (LDO6)
VCCIO_SD: C5002.1, C15013.1, U3001.T13 (VCCIO2_VDD), U13001.5 (LDO8)
VCC_0V8: C10003.1, C15006.1, R7004.1, U3001.R6 (USB_AVDD_0V8), U13001.23 (LDO1)
VCC_0V8_PMU: C15008.1, C23004.1, C23005.1, U3001.P11 (PLL_AVDD_0V8), U13001.20 (LDO3)
VCC_1V8: C6001.1, C6003.1, C6005.1, C6007.1, C7002.1, C10002.1, C15009.1, R6006.2, R6007.2, R7003.1, U3001.P6 (VCCIO1_VDD), U3001.P15 (VCCIO4_VDD), U3001.R7 (USB_AVDD_1V8), U6001.C6 (V_{CCQ}), U6001.M4 (V_{CCQ}), U6001.N4 (V_{CCQ}), U6001.P3 (V_{CCQ}), U6001.P5 (V_{CCQ}), U13001.28 (LDO4)
VCC_1V8_PMU: C15007.1, C23006.1, C23007.1, U3001.R11 (PLL_AVDD_1V8), U13001.21 (LDO2)
VCC_3V3: C6004.1, C6006.1, C10001.1, C15015.1, Q10001.3 (C), R10002.1, U3001.T7 (USB_AVDD_3V3), U6001.E6 (V_{CC}), U6001.F5 (V_{CC}), U6001.J10 (V_{CC}), U6001.K9 (V_{CC}), U13001.58 (SWOUT2)
VCC_3V3_SD: C5001.1, C5003.1, C15014.1, D5005.1 (A1), J5001.4 (VDD), U13001.6 (LDO9)
VCC_5V0: C15016.1, U13001.55 (SWOUT1)
VCC_BUCK5: C15001.1, C15002.1, C15017.1, C15018.1, L15001.1, R2001.1, U13001.22 (VCC5), U13001.30 (VCC6), U13001.59 (FB5)
VCC_DDR: C3001.2, C3003.2, C3004.2, C3005.2, C3006.2, C3007.2, C14010.1, C14012.1, C18002.2, C18003.2, C18005.2, C18006.2, C18007.2, C18009.2, C18010.2, C18012.2, C18013.2, C18015.2, C18016.2, C18018.2, C18019.2, C18021.2, C18022.2, C18024.2, C18025.2, C18027.2, C18028.2, C18029.2, C18030.2, C18031.2, C18032.2, C18033.2, C18034.2, C18035.2, C18036.2, C18037.2, C18038.2, C18039.2, C18040.2, C18041.2, L14003.1, R14004.1, R17004.1, U3001.G7 (DDR_VDD1), U3001.G8 (DDR_VDD2), U3001.G9 (DDR_VDD3), U3001.H8 (DDR_VDD4), U3001.J7 (DDR_VDD5), U3001.K7 (DDR_VDD6), U3001.L7 (DDR_VDD7), U13001.26 (VBUCK3), U17002.A1 (V_{DDQ}), U17002.A9 (V_{DDQ}), U17002.B3 (V_{DD}), U17002.B9 (V_{DD}), U17002.C1 (V_{DDQ}), U17002.D1 (V_{DD}), U17002.D9 (V_{DDQ}), U17002.F2 (V_{DDQ}), U17002.F8 (V_{DDQ}), U17002.G1 (V_{DDQ}), U17002.G7 (V_{DD}), U17002.G9 (V_{DDQ}), U17002.J1 (V_{DD}), U17002.J2 (V_{DDQ}), U17002.J8 (V_{DDQ}), U17002.J9 (V_{DD}), U17002.L1 (V_{DD}), U17002.L9 (V_{DD}), U17002.R1 (V_{DD}), U17002.T9 (V_{DD}), U17003.A1 (V_{DDQ}), U17003.A9 (V_{DDQ}), U17003.B3 (V_{DD}), U17003.B9 (V_{DD}), U17003.C1 (V_{DDQ}), U17003.D1 (V_{DD}), U17003.D9 (V_{DDQ}), U17003.F2 (V_{DDQ}), U17003.F8 (V_{DDQ}), U17003.G1 (V_{DDQ}), U17003.G7 (V_{DD}), U17003.G9 (V_{DDQ}), U17003.J1 (V_{DD}), U17003.J2 (V_{DDQ}), U17003.J8 (V_{DDQ}), U17003.J9 (V_{DD}), U17003.L1 (V_{DD}), U17003.L9 (V_{DD}), U17003.R1 (V_{DD}), U17003.T9 (V_{DD})
VDD_1V8_PMU: C12014.1, U3001.H14 (VCCIO_VDD_1V8)
VDD_ARM: C12002.1, C12005.1, C12007.1, C12009.1, C14002.1, C14004.1, C14006.1, L14002.1, R14002.1, R14002.2, U3001.N12 (ARM_VDD_1), U3001.P12 (ARM_VDD_2), U3001.P13 (ARM_VDD_3), U13001.8 (FB2)
VDD_LOGIC: C2003.1, C2004.1, C2005.1, C2006.2, C12020.1, C12022.1, L2001.2, R2002.1, R2002.2, R2003.2, U3001.H9 (LOGIC_VDD_1), U3001.J9 (LOGIC_VDD_3), U3001.J13 (LOGIC_VDD_4), U3001.M11 (LOGIC_VDD_6)
VDD_NPU: C12001.1, C12003.1, C12004.1, C12006.1, C12008.1, C12010.1, C12011.1, C12013.1, C12015.1, C12016.1, C12019.1, C12022.2, C14001.1, C14003.1, C14005.1, L14001.1, R14001.1, R14001.2, U3001.G10 (VSS_29), U3001.H10 (VSS_37), U3001.H11 (NPU_VDD_1), U3001.J10 (NPU_VDD_3), U3001.J11 (NPU_VDD_4), U3001.K10 (NPU_VDD_5), U3001.K11 (NPU_VDD_6), U3001.L9 (VEPU_VDD_1), U3001.M9 (VEPU_VDD_2), U3001.N8 (VEPU_VDD_3), U13001.13 (FB1)

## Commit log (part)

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2023-02-25 updated DDR Power
2023-02-25 updated DDR
2023-02-25 changed to use GND instead of GNDD and GNDA
2023-02-25 updated DDR data lines
2023-02-25 updated Block size
2023-02-25 updated Power GND
2023-02-25 updated Block size & pos
2023-02-25 added MicroSD
2023-02-26 added USB
2023-02-28 added SDCard
2023-02-28 updated USB OTG
2023-02-28 Rename SDCard sheet
2023-03-01 Updated eMMC
2023-03-02 link FLASH_VOL_SEL
2023-03-02 added blank Ethernet
2023-03-02 MIPI-DSI block
2023-03-03 Updated:
    Added Display
    Rename DDR to DDR3
2023-03-03 rename DDR3 back to DDR
2023-03-04 added Wifi (AP6256)
2023-03-04 updated footprints
2023-03-04 added mini pcie board
2023-03-04 updated Reference, and PCB
2023-03-05 updated LCSC selection of capacitors
2023-03-05 updated PCB Design Rules
2023-03-06 updated DDR_VDD
2023-03-06 updated foorprints
2023-03-07 layout SoC Power and DDR capacitors
2023-03-07 rearrange ICs position
2023-03-07 updated Resistors
2023-03-08 updated PMIC
2023-03-09 remove WiFI module
2023-03-09 replace DDR_2V5 LDO component
2023-03-09 added missing pins
2023-03-09 updated emmc and rv1126 footprints
2023-03-10 moved DDR_VREFCA to DDR Power
2023-03-11 added VDD Logic
2023-03-11 updated for ERC
2023-03-12 fix ERC
2023-03-12 updated symbols
2023-03-12 fixing warnings
2023-03-12 fix warnings
2023-03-12 fix ERC warnings
2023-03-13 added OSC, updated annotations
2023-03-13 added more capacitors for second DDR4
2023-03-13 added Decoupling C for PMUIO_0V8/1V8
2023-03-13 placed DDR Capacitors
2023-03-13 placed RK809 components
2023-03-14 updated pos
2023-03-14 added extended board length
2023-03-14 setup Design Rules
2023-03-15 setup basic PCB Design Rules
2023-03-15 setup RULES
2023-03-16 setup PWR netclass
2023-03-16 rename emmc to vccio1
2023-03-16 rename Camera to VCCIO4
2023-03-16 rename sub sheets name
2023-03-16 rename SDCard to VCCIO2
2023-03-16 rename USB OTG to USB
2023-03-16 updated PCB nets from schematic
2023-03-16 updated Via spec as RK template
2023-03-16 setup PWR via
2023-03-16 updated Design Rules
2023-03-16 fan out SoC
2023-03-16 changed Stack Up
2023-05-13 old missing commits
2023-05-13 new commits
2023-05-13 route DDR_D30
2023-05-15 move old minipcie board into sub dir
2023-05-17 replace DDR4 chips with Hierachical Sheets module
2023-05-17 remove old DDR U4B
2023-05-17 move DDR power decoupling capacitors into DDR4 Sheet
2023-05-17 changed Power Label and copy DDR4 Sheets
2023-05-17 added more capacitors for 2v5 output
2023-05-17 remove DDR decoupling capacitors sheets
2023-05-17 resort all symbols
2023-05-17 connect new decoupling capacitors
2023-05-17 fix naming
2023-05-17 remove DRC errors
2023-05-17 added nettile for DCDC feedback
2023-05-17 update components footprint and LCSC; update RV1126 symbol
2023-05-17 updated annotations
2023-06-06 changed In3 layer name, updated Custom Design Rules
2023-06-06 better looking of DDR capacitors
2023-06-06 placed some DDR capacitors
2023-06-06 replace DDR capacitors of 0201 to 0402
2023-06-06 placed capacitors for one DDR4
2023-06-06 fix one capacitor of one DDR
2023-06-07 added one 22uF. Finish DDR capacitors
2023-06-07 fanout SoC DDR
2023-06-07 added Diff 100R custom design rules
2023-06-07 switch pos of two DDR subsheet
2023-06-07 removed CLK_P/N vias
2023-06-07 changed Physical Stackup and Custom Rules
2023-06-07 added more net classes
2023-06-07 added two more capacitors
2023-06-07 updated layer settings
2023-06-07 added README and license
2023-06-07 route DDR4_A12
2023-06-07 rotate resistor networks
2023-06-07 route DDR4_A6 and A0
2023-06-07 routed DDR4_A11
2023-06-07 arrange more DDR resistors
2023-06-07 switch DDR Sheet /1
2023-06-07 switched DDR Data Lines
2023-06-07 connect DDR4_DQS3N/P
2023-06-07 connect DDR4_DQS1N/P
2023-06-07 connect DDR4_DQS0N/P
2023-06-07 connect DDR4_DQS2N/P
2023-06-07 connect DDR4_A9/A7
2023-06-07 routed DDR4 A16
2023-06-07 replace VREF resistors
2023-06-07 replaced and placed DDR VREF caps and res
2023-06-07 routed A15
2023-06-07 shfited SoC DDR up
2023-06-07 routed DDR4 A5
2023-06-07 fix corners
2023-06-07 routed DDR4 A2
2023-06-08 fix Q1
    was flipped
2023-06-08 routed DDR4 A10
2023-06-08 fixed and routed DDR4 BG0
2023-06-08 routed DDR4 A4
2023-06-08 routed DDR4 BA1
2023-06-08 routed DDR4 ODT0 and ACTn
2023-06-08 routed CS0
2023-06-08 added more 50R netclasses
2023-06-08 re-routed DDR4 CS0n
2023-06-08 re-routed DDR4 ODT0 with 50R
2023-06-08 added missing 1nF capacitor for DDR_RESET
2023-06-08 routed DDR4_RESETn
2023-06-09 fix DDR4 DM3/1
2023-06-09 routed DDR4 CKE
2023-06-09 routed DDR4 BA0
2023-06-09 routed DDR4 DDR4 D27
2023-06-09 routed DDR4 DDR4 D29
2023-06-09 routed DDR4 D8/9
2023-06-09 rerouted DDR4 DQS1N/P
2023-06-09 routed DDR4 D14
2023-06-09 routed DDR4 D31
2023-06-09 fix DDR4 ODT0 netclass
2023-06-09 routed DDR4 D25/24
2023-06-09 routed DDR4 D13
2023-06-09 routed DDR4 D12 D10 D28
2023-06-09 routed DDR4 D11
2023-06-09 removed one duplicated route
2023-06-09 routed more 2nd DDR
2023-06-09 routed more 2nd DDR address lines
2023-06-09 routed more 2nd DDR data lines
2023-06-09 rearranged caps res
2023-06-09 adjusted routed
2023-06-09 adjusted track width of DDR4 A1
2023-06-09 adjusted track width of DDR4 A7
2023-06-09 routed PWRs for 1st DDR
2023-06-10 routed more PWRs
2023-06-10 routed PWRs for 2nd DDR
2023-06-10 routed D0/D5 for 2nd DDR4
2023-06-10 re-routed DDR4 CKE and ODT0
2023-06-10 routed DDR4 TEN PAR
2023-06-10 routed DDR4 PWRs and CLK
2023-06-10 routed DDR4 PWRs
2023-06-10 added predefined 50R outer track width
2023-06-10 routed more DDR PWRs
2023-06-10 finishing DDR wires
2023-06-10 minimize DDR A9
2023-06-10 length matching to CLK_N/P
2023-06-11 updated design rules
    1. route 50R matched impedance with 0.1mm inside BGA footprint.
2023-06-11 updated some routes following new rules
2023-06-11 move eMMC away, move SoC and DDR to center
2023-06-11 changed some matched impedance routes
2023-07-09 ignore kicad_prl
2023-08-24 moved (a bit) SoC DDR part
2023-08-24 refined DDR netclasses
2023-08-25 updated custom DRC rules for HuaQiu 06161H01-1080 Stack up
2023-08-25 updated custom Design Rules
2023-09-30 replaced local cloned symbols
2023-09-30 replaced Leaf libraries with combined libraries
2023-09-30 updated constraints
2023-09-30 updated impedance matching constraints
2023-10-22 updated some routes
2023-10-22 re-routed DDR4_CLK
    changed netclass for DDR4_CLK (DP_80R)
    updated custom designed rules
    changed netname from CLKN/P to CLK_N/P
2023-10-22 updated .gitattributes
2023-10-22 changed netclasses
2023-10-22 updated PCB Physical Stackup
2023-11-17 updated schematics due to upgrade to 7.99
2023-11-17 updated due to upgrade to 7.99
2023-11-17 routing DDR
2023-11-17 updated PCB
2023-11-26 adjust / fix routing
2023-11-27 tuning length of DDR Data 0 bus
2023-11-27 updated project due to merge of ipc 2581
2023-11-27 tuned DDR CLK traces
2023-11-28 changed DDR4_CLK tuning
2023-11-28 swap ln2_Pwr with ln3_Signal and moved trackes on ln3
    According to TI's DDR4 Board Design and Layout Guidance,
    it is better to transition to a layer using same reference layer.
2023-11-28 remove branches of DDR4_CLK
2023-11-28 routed and tuned from DDR4_CLK to DDR4_CLK_B
2023-11-28 remove DNP of termination capacitor of DDR4_CLK
2023-11-28 remove some DDR address lines from pad to intermediate resistors
2023-11-28 tuned skew of DDR CLK
2023-11-28 remove some T-branch of address lines
2023-11-28 removed more DDR pads to reistor tracks
2023-12-01 remove vias height from track length, changed default tuning pattern
2023-12-01 updated schematics due to kicad master upgrades
2023-12-01 connect to DDR4_A9
2023-12-01 added 'BGA Pad Clearance'
    set to 0.1mm
2023-12-01 unified multiple DDR4_ netclasses into one
2023-12-01 updated netclasses
2023-12-01 updated DDR4 Data Lane 0 routes
2023-12-01 changed via clearance under BGAs
2023-12-01 changed BGA exceptions under U2, U7, U8
2023-12-02 added exception of track clearance under BGA
2023-12-02 fix typo of file name
2023-12-11 routed D1/D4
2023-12-11 clean up sch due to KiCad upgrade
2023-12-11 connect most of GNDs and VCCs
2023-12-11 remove one skew tuning pattern for DDR4_CLK
2023-12-11 remove one 100nF capacitor in DDR4_Sheet
2023-12-11 remove two 100nF capacitors in DDR4_Sheet for routing
2023-12-11 length matching A9, A8
2023-12-11 routed DDR4_A7
2023-12-13 tuned more length matching
2023-12-13 tuned more traces
2023-12-14 redo length matching
2023-12-15 locked several tracks after length tuning
2023-12-15 length tuned DDR4_A10
2023-12-15 length tuned DDR4_A1, A8
2023-12-15 length tuned DDR4_A2, A0, A6
2023-12-15 length tuned DDR4_BG0
2023-12-15 length tuned DDR4_A5, A3, BA1
2023-12-15 length tuned DDR4_nCAS, nACT
2023-12-15 length tuned DDR4_nCS0
2023-12-15 length tuning of DDR4_A12
2023-12-15 length tuning of DDR4_ODT0
2023-12-15 length tuning of DDR4_CKE
2023-12-15 tuning DDR4_CLK
2023-12-16 redo length tuning of DDR4_A4, BA0
2023-12-16 redo length tuning of DDR4_nRAS
2023-12-16 redo length tuning of DDR4_BG0
2023-12-16 redo length tuning of DDR4_A12
2023-12-16 redo length tuning of DDR4_nRAS, to make room for DDR4_nWE
2023-12-16 redo length tuning of DDR4_A10, to make room for DDR4_CKE
2023-12-16 redo length tuning of DDR4_BG0, to make room for DDR4_CKE
2023-12-16 redo length tuning of DDR4_A12, to make room for DDR4_CKE
2023-12-16 redo length tuning of DDR4_RAS, to make room for DDR4_CKE
2023-12-16 redo length tuning of DDR4_CKE, ODT0
2023-12-16 checks and tuning
2023-12-16 routed DDR4_DQS3
2023-12-16 locked DDR4_D27
2023-12-16 length tuning of DDR4_DM3
2023-12-16 length tuning of DDR4_D30
2023-12-16 added one GND via
2023-12-16 length tuning of DDR4_D28,D29
2023-12-16 length tuning of DDR4_D25,D26
2023-12-16 locked DDR4_D0, unlocked DDR4_D6
2023-12-16 skew tuned of DDR4_DQS0
2023-12-16 remove one GND via
2023-12-16 tuned and relocked DDR4_D0
2023-12-16 length tuning of DDR4_D4
2023-12-16 length tuning of DDR4_D1
2023-12-16 try to tuning DDR4_DQS0
2023-12-16 length tuned DDR4_DQS0
2023-12-16 length tuned DDR4_D0 to match DDR4_D6
2023-12-16 length tuned DDR4_D5 to match DDR4_D6
2023-12-16 length tuned DDR4_D4 to match DDR4_D6
2023-12-16 length tuned DDR4_D1 to match DDR4_D6
2023-12-16 recheck length of match DDR4_D6
2023-12-16 redo length tuning of DDR4_D0 to match DDR4_D6
2023-12-16 redo length tuning of DDR4_D5 to match DDR4_D6
2023-12-16 redo length tuning of DDR4_D4 to match DDR4_D6
2023-12-16 redo length tuning of DDR4_D1 to match DDR4_D6
2023-12-16 redo length tuning of DDR4_D3 and D2 to match DDR4_D6
2023-12-16 redo length tuning of DDR4_CS0, length tuned for DDR4_D15, D14
2023-12-16 try to tuning Data Lane 1 ( D8-D15 )
2023-12-20 re-tuned length of DDR4_D31, DM3
2023-12-20 re-tuned length of DDR4_D14
2023-12-20 re-tuned length of DDR4_D9
2023-12-21 arrange wires in DDR Data Lanes
2023-12-21 re-routed DDR4_DQS1
2023-12-21 length matched DDR4_DQS1
2023-12-21 length matched DDR4_D12
2023-12-21 length matched DDR4_D10
2023-12-21 length matched DDR4_D11
2023-12-21 locked DDR4_DM2
2023-12-21 tuned length of DDR4_D22
2023-12-21 tuned length of DDR4_DQS2
2023-12-21 re-tuned length of DDR4_DQS2
2023-12-21 tuned length of DDR4_D20
2023-12-21 tuned length of DDR4_D19
2023-12-21 re-tuned length of DDR4_D19, to make room for D18
2023-12-21 tuned length of DDR4_D18
2023-12-21 tuned length of DDR4_D17
2023-12-21 try to re-tune length of DDR4_D17
2023-12-21 re-tuned length of DDR4_D12
2023-12-21 re-tuned length of DDR4_D17
2023-12-21 tuned length of DDR4_D16
2023-12-23 a state of submission of an issue of differential pair
2024-01-09 redo length tuning of DDR4_ODT0 and CKE
2024-01-09 redo length tuning of DDR4 CLK_P/N
2024-01-12 connecting second DDR4_CLK branch to U7 ( from U8 )
2024-01-12 re-route length tuning of DDR4 RAS & nACT
2024-01-13 adjust serverl tracks, and routed BA1
2024-01-13 routing nCS0
2024-01-13 routed second branch of DDR4_A10
2024-01-13 re-position several resistors
2024-01-13 fix positioning of one DDR Power Capacitor
2024-01-13 fix routing segments
2024-01-25 small changes on PCB
2024-01-25 adjust DDR4_CLK_NP
2024-01-25 tuning skew of DDR4_CLK_NP
2024-01-26 updated layer names
    due to kicad version upgrade
2024-01-26 remove extra track
2024-01-26 make room for DDR4_nRESET
